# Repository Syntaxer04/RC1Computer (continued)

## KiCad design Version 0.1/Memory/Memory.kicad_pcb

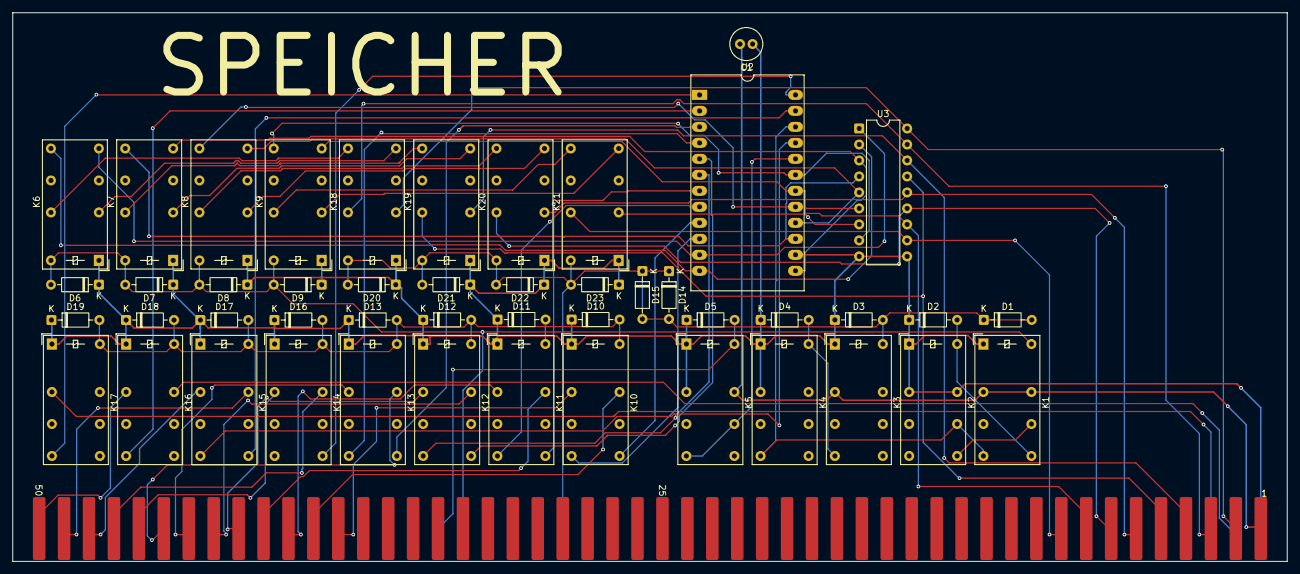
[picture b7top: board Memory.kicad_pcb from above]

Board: 2 copper layers, 202.4 x 87.1 mm, 48 parts (0 on the bottom side), 63 nets.

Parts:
C1: C; C_Radial_D5.0mm_H11.0mm_P2.00mm
D1, D2, D3, D4, D5, D6, D7, D8, D9, D10, D11, D12, D13, D14, D15, D16, D17, D18, D19, D20, D21, D22, D23: 1N914; D_DO-35_SOD27_P7.62mm_Horizontal
K1, K2, K3, K4, K5, K6, K7, K8, K9, K10, K11, K12, K13, K14, K15, K16, K17, K18, K19, K20, K21: HK19F-DCxxV-SHC; Relay_DPDT_Finder_30.22
U1: Conn_RC_Male_100
U2: CY62256-70PC; DIP-24_18.0mmx34.29mm_W15.24mm_LongPads
U3: ULN2803A; DIP-18_W7.62mm

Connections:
+5V: C1.2, K1.11, K1.21, K3.11, K5.21, U1.1 (5_Volt)
A0: K10.11, U1.38 (A0)
A1: K10.21, U1.39 (A1)
A2: K11.11, U1.40 (A2)
A3: K11.21, U1.41 (A3)
A4: K12.11, U1.42 (A4)
A5: K12.21, U1.43 (A5)
A6: K13.11, U1.44 (A6)
A7: K13.21, U1.45 (A7)
A8: K14.11, U1.46 (A8)
A9: K14.21, U1.47 (A9)
A10: K15.11, U1.48 (A10)
A11: K15.21, U1.49 (A11)
A12: K16.11, U1.50 (A12)
A13: K16.21, U1.52 (A13)
A14: K17.11, U1.53 (A14)
AI0: K10.14, U2.10 (A0)
AI1: K10.24, U2.9 (A1)
AI2: K11.14, U2.8 (A2)
AI3: K11.24, U2.7 (A3)
AI4: K12.14, U2.6 (A4)
AI5: K12.24, U2.5 (A5)
AI6: K13.14, U2.4 (A6)
AI7: K13.24, U2.3 (A7)
AI9: K14.24, U2.24 (A9)
AI10: K15.14, U2.21 (A10)
AI11: K15.24, U2.23 (A11)
AI12: K16.14, U2.2 (A12)
AI14: K17.14, U2.1 (A14)
CS: K5.14, K5.22, U2.20 (~CS)
D0: K6.11, K18.14
D1: K6.21, K18.24
D2: K7.11, K19.14
D3: K7.21, K19.24
D4: K8.11, K20.14
D5: K8.21, K20.24
D6: K9.11, K21.14
D7: K9.21, K21.24
DO0: K18.11, U1.2 (D0), U3.18 (O1)
DO1: K18.21, U1.3 (D1), U3.17 (O2)
DO2: K19.11, U1.4 (D2), U3.16 (O3)
DO3: K19.21, U1.5 (D3), U3.15 (O4)
DO4: K20.11, U1.6 (D4), U3.14 (O5)
DO5: K20.21, U1.7 (D5), U3.13 (O6)
DO6: K21.11, U1.8 (D6), U3.12 (O7)
DO7: K21.21, U1.9 (D7), U3.11 (O8)
GND: C1.1, D2.1 (K), D3.1 (K), D4.1 (K), D5.1 (K), D6.1 (K), D7.1 (K), D8.1 (K), D9.1 (K), D10.1 (K), D11.1 (K), D12.1 (K), D13.1 (K), D16.1 (K), D17.1 (K), D18.1 (K), D19.1 (K), D20.1 (K), D21.1 (K), D22.1 (K), D23.1 (K), K1.A1, K2.11, K2.21, K2.A1, K3.A1, K4.11, K4.A1, K5.11, K5.A1, K6.A1, K7.A1, K8.A1, K9.A1, K10.A1, K11.A1, K12.A1, K13.A1, K14.A1, K15.A1, K16.A1, K17.A1, K18.A1, K19.A1, K20.A1, K21.A1, U1.51 (GND), U2.14 (GND), U3.9 (GND), U3.10 (COM)
MEMREAD: D1.1 (K), D1.2 (A), D3.2 (A), D14.1 (K), D14.2 (A), D15.1 (K), D15.2 (A), D20.2 (A), D21.2 (A), D22.2 (A), D23.2 (A), K3.A2, K18.A2, K19.A2, K20.A2, K21.A2, U1.79 (MEMREAD)
MEMSel: D5.2 (A), K5.A2, U1.84 (MEMSL)
MEMWRITE: D6.2 (A), D7.2 (A), D8.2 (A), D9.2 (A), K1.A2, K6.A2, K7.A2, K8.A2, K9.A2, U1.83 (MEMWRITE)
unnamed: D2.2 (A), K1.24, K2.A2
unnamed: D4.2 (A), K3.14, K4.A2
unnamed: D10.2 (A), D11.2 (A), D12.2 (A), D13.2 (A), D16.2 (A), D17.2 (A), D18.2 (A), D19.2 (A), K10.A2, K11.A2, K12.A2, K13.A2, K14.A2, K15.A2, K16.A2, K17.A2
unnamed: K6.14, U2.11 (Q0), U3.1 (I1)
unnamed: K6.24, U2.12 (Q1), U3.2 (I2)
unnamed: K7.14, U2.13 (Q2), U3.3 (I3)
unnamed: K7.24, U2.15 (Q3), U3.4 (I4)
unnamed: K8.14, U2.16 (Q4), U3.5 (I5)
unnamed: K8.24, U2.17 (Q5), U3.6 (I6)
unnamed: K9.14, U2.18 (Q6), U3.7 (I7)
unnamed: K9.24, U2.19 (Q7), U3.8 (I8)
OE: K1.14, K2.22, K4.14, U2.22 (~OE)
WE: K1.22, K2.24
